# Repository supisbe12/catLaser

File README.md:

catLaser
---
A camera watches the room for your cat. When it detects motion, it figures out which direction the cat is moving and swings a laser dot slightly ahead of that movement — so the cat is always chasing something just out of reach rather than sitting on top of it. When the cat is finished it will point the laser at a dropper that will dispense treats. or when the cat disappears for a few seconds, it does a slow sweep to re-bait attention. After three minutes of nothing, it shuts the laser off and parks itself to save battery.
---
Screenshots
---

---
Hardware

Microcontroller: ESP32-S3-WROOM-1-N16R8 (Dual-core Xtensa LX7 @ up to 240MHz, 16MB Flash, 8MB Octal PSRAM)
Camera: Taidacent OV2640 2MP, connected via 24-pin 0.5mm FPC ribbon cable + ZIF socket
Power: Single 18650 Li-ion cell, onboard TP4056 charging via USB-C, MT3608 boost converter (stable 5V rail), AMS1117-3.3 LDO (3.3V rail)
Mounting: 3M Dual Lock strips — peel off to charge, click back into the same spot
---
Software
Unfinished(need parts)
---
Bill of Materials
https://docs.google.com/spreadsheets/d/1QPfYICotrgUIVAbHsGZsmmrA3oqBLHhNqElr4AwxpG0/edit?usp=sharing

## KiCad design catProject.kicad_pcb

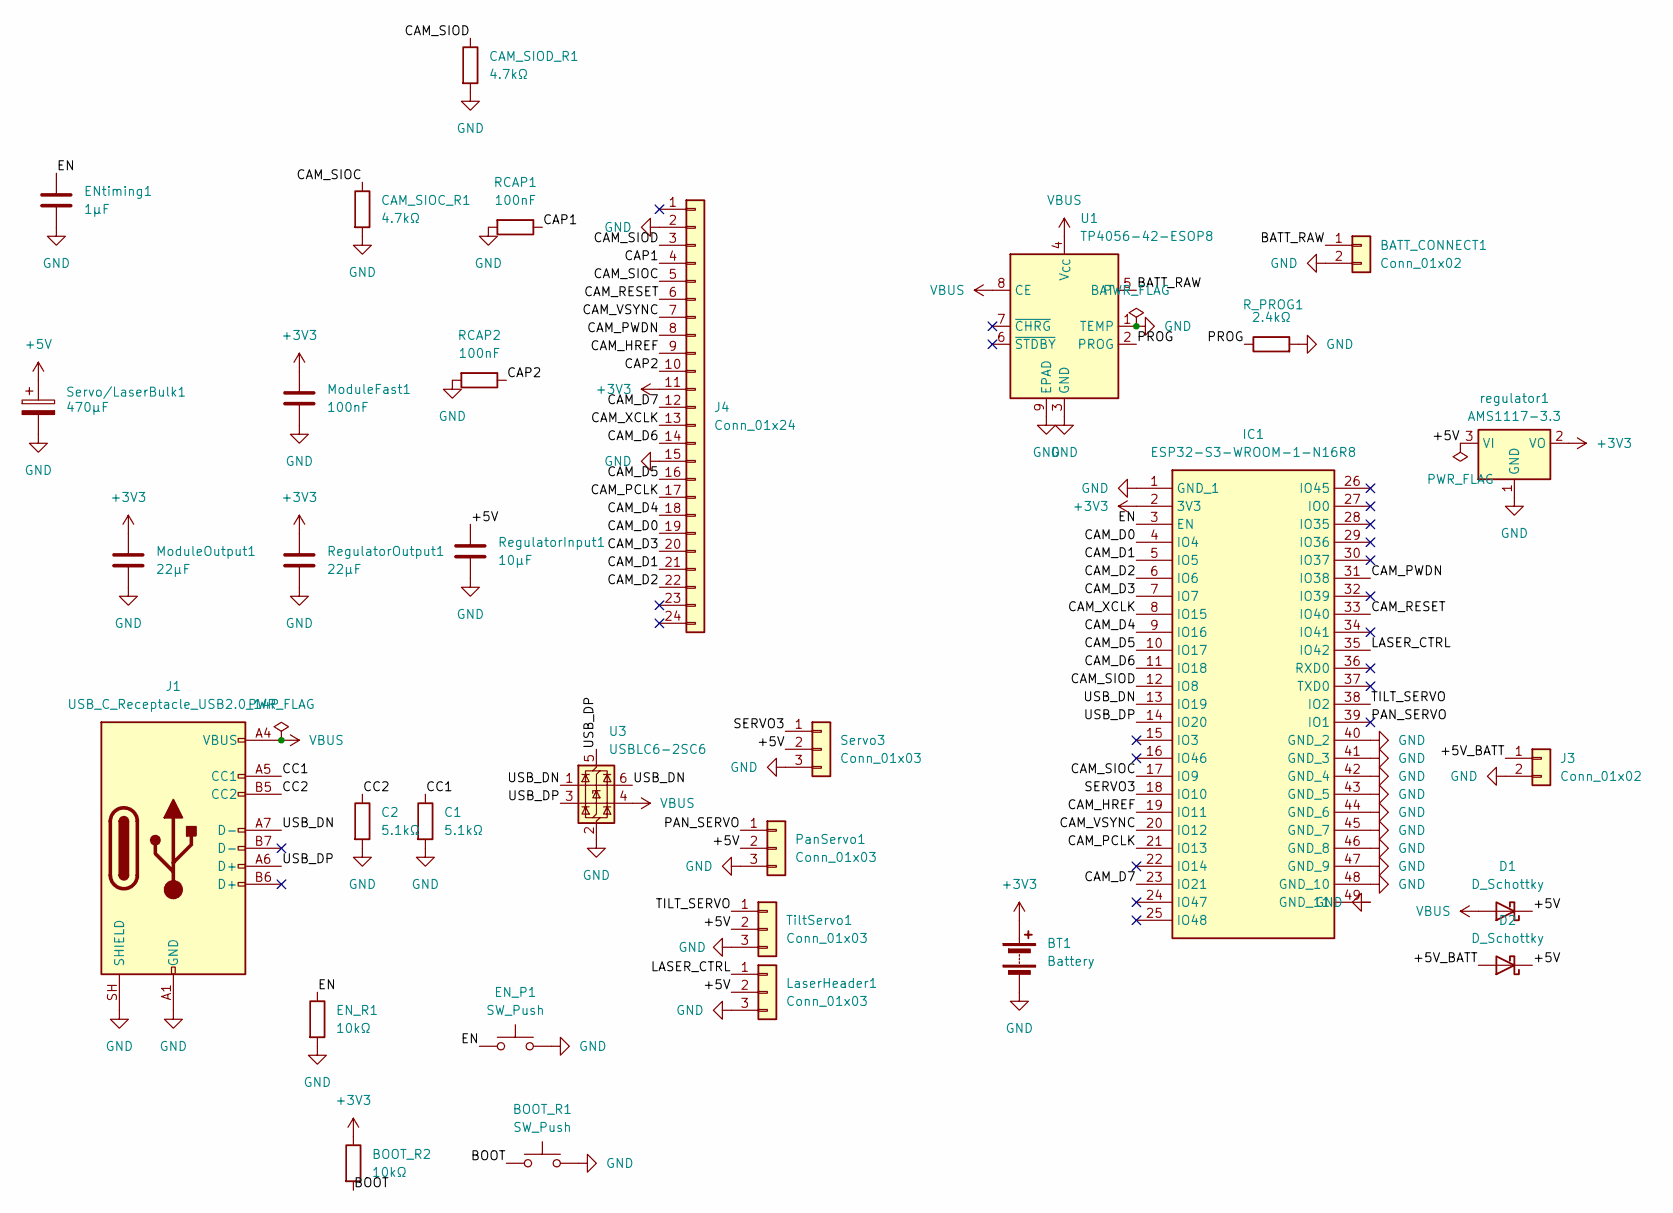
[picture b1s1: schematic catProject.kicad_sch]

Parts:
BATT_CONNECT1: Conn_01x02; PinHeader_1x02_P2.54mm_Vertical
BOOT_R1: SW_Push; SW_PUSH_6mm
BOOT_R2: 10kΩ; R_0805_2012Metric
BT1: Battery
C1, C2: 5.1kΩ; R_0805_2012Metric
CAM_SIOC_R1: 4.7kΩ
CAM_SIOD_R1: 4.7kΩ
D1, D2: D_Schottky; D_SMA
EN_P1: SW_Push; SW_PUSH_6mm
EN_R1: 10kΩ; R_0805_2012Metric
ENtiming1: 1µF; C_0805_2012Metric
IC1: ESP32-S3-WROOM-1-N16R8; ESP32S3WROOM1N16R8; Mouser Part Number 356-ESP32S3WRM1N16R8
J1: USB_C_Receptacle_USB2.0_14P; USB_C_Receptacle_GCT_USB4105-xx-A_16P_TopMnt_Horizontal
J3: Conn_01x02; PinHeader_1x02_P2.54mm_Vertical
J4: Conn_01x24; Hirose_FH12-24S-0.5SH_1x24-1MP_P0.50mm_Horizontal
LaserHeader1: Conn_01x03; PinHeader_1x03_P2.54mm_Vertical
ModuleFast1: 100nF; C_0805_2012Metric
ModuleOutput1: 22µF; C_0805_2012Metric
PanServo1: Conn_01x03; PinHeader_1x03_P2.54mm_Vertical
RCAP1, RCAP2: 100nF; R_0805_2012Metric
R_PROG1: 2.4kΩ; R_0805_2012Metric
RegulatorInput1: 10µF; C_0805_2012Metric
RegulatorOutput1: 22µF; C_0805_2012Metric
Servo3: Conn_01x03; PinHeader_1x03_P2.54mm_Vertical
Servo/LaserBulk1: 470µF; CP_Radial_D6.3mm_P2.50mm
TiltServo1: Conn_01x03; PinHeader_1x03_P2.54mm_Vertical
U1: TP4056-42-ESOP8; SOIC-8-1EP_3.9x4.9mm_P1.27mm_EP2.41x3.3mm
U3: USBLC6-2SC6; SOT-23-6
regulator1: AMS1117-3.3; SOT-223-3_TabPin2

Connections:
+3V3: BOOT_R2.1, BT1.1 (+), IC1.2 (3V3), J4.11, ModuleFast1.1, ModuleOutput1.1, RegulatorOutput1.1, regulator1.2 (VO)
+5V: D1.1 (K), D2.1 (K), LaserHeader1.2, PanServo1.2, RegulatorInput1.1, Servo3.2, Servo/LaserBulk1.1, TiltServo1.2, regulator1.3 (VI)
/+5V_BATT: D2.2 (A), J3.1
/BATT_RAW: BATT_CONNECT1.1, U1.5 (BAT); also elsewhere on the board
/BOOT: BOOT_R1.1, BOOT_R2.2
/CAM_D0: IC1.4 (IO4), J4.19
/CAM_D1: IC1.5 (IO5), J4.21
/CAM_D2: IC1.6 (IO6), J4.22
/CAM_D3: IC1.7 (IO7), J4.20
/CAM_D4: IC1.9 (IO16), J4.18
/CAM_D5: IC1.10 (IO17), J4.16
/CAM_D6: IC1.11 (IO18), J4.14
/CAM_D7: IC1.23 (IO21), J4.12
/CAM_HREF: IC1.19 (IO11), J4.9
/CAM_PCLK: IC1.21 (IO13), J4.17
/CAM_PWDN: IC1.31 (IO38), J4.8
/CAM_RESET: IC1.33 (IO40), J4.6
/CAM_SIOC: CAM_SIOC_R1.1, IC1.17 (IO9), J4.5
/CAM_SIOD: CAM_SIOD_R1.1, IC1.12 (IO8), J4.3
/CAM_VSYNC: IC1.20 (IO12), J4.7
/CAM_XCLK: IC1.8 (IO15), J4.13
/CAP1: J4.4, RCAP1.1
/CAP2: J4.10, RCAP2.1
/CC1: C1.1, J1.A5 (CC1)
/CC2: C2.1, J1.B5 (CC2)
/EN: EN_P1.1, EN_R1.1, ENtiming1.1, IC1.3 (EN)
/LASER_CTRL: IC1.35 (IO42), LaserHeader1.1
/PAN_SERVO: IC1.39 (IO1), PanServo1.1
/PROG: R_PROG1.1, U1.2 (PROG)
/SERVO3: IC1.18 (IO10), Servo3.1
/TILT_SERVO: IC1.38 (IO2), TiltServo1.1
/USB_DN: IC1.13 (IO19), J1.A7 (D-), U3.1 (I/O1), U3.6 (I/O1)
/USB_DP: IC1.14 (IO20), J1.A6 (D+), U3.3 (I/O2), U3.5 (VBUS)
GND: BATT_CONNECT1.2, BOOT_R1.2, BT1.2 (-), C1.2, C2.2, CAM_SIOC_R1.2, CAM_SIOD_R1.2, EN_P1.2, EN_R1.2, ENtiming1.2, IC1.1 (GND_1), IC1.40 (GND_2), IC1.41 (GND_3), IC1.42 (GND_4), IC1.43 (GND_5), IC1.44 (GND_6), IC1.45 (GND_7), IC1.46 (GND_8), IC1.47 (GND_9), IC1.48 (GND_10), IC1.49 (GND_11), J1.A1 (GND), J1.A12 (GND), J1.B1 (GND), J1.B12 (GND), J1.SH (SHIELD), J3.2, J4.2, J4.15, LaserHeader1.3, ModuleFast1.2, ModuleOutput1.2, PanServo1.3, RCAP1.2, RCAP2.2, R_PROG1.2, RegulatorInput1.2, RegulatorOutput1.2, Servo3.3, Servo/LaserBulk1.2, TiltServo1.3, U1.1 (TEMP), U1.3 (GND), U1.9 (EPAD), U3.2 (GND), regulator1.1 (GND); also elsewhere on the board
VBUS: D1.2 (A), J1.A4 (VBUS), J1.A9 (VBUS), J1.B4 (VBUS), J1.B9 (VBUS), U1.4 (V_{CC}), U1.8 (CE), U3.4 (I/O2)

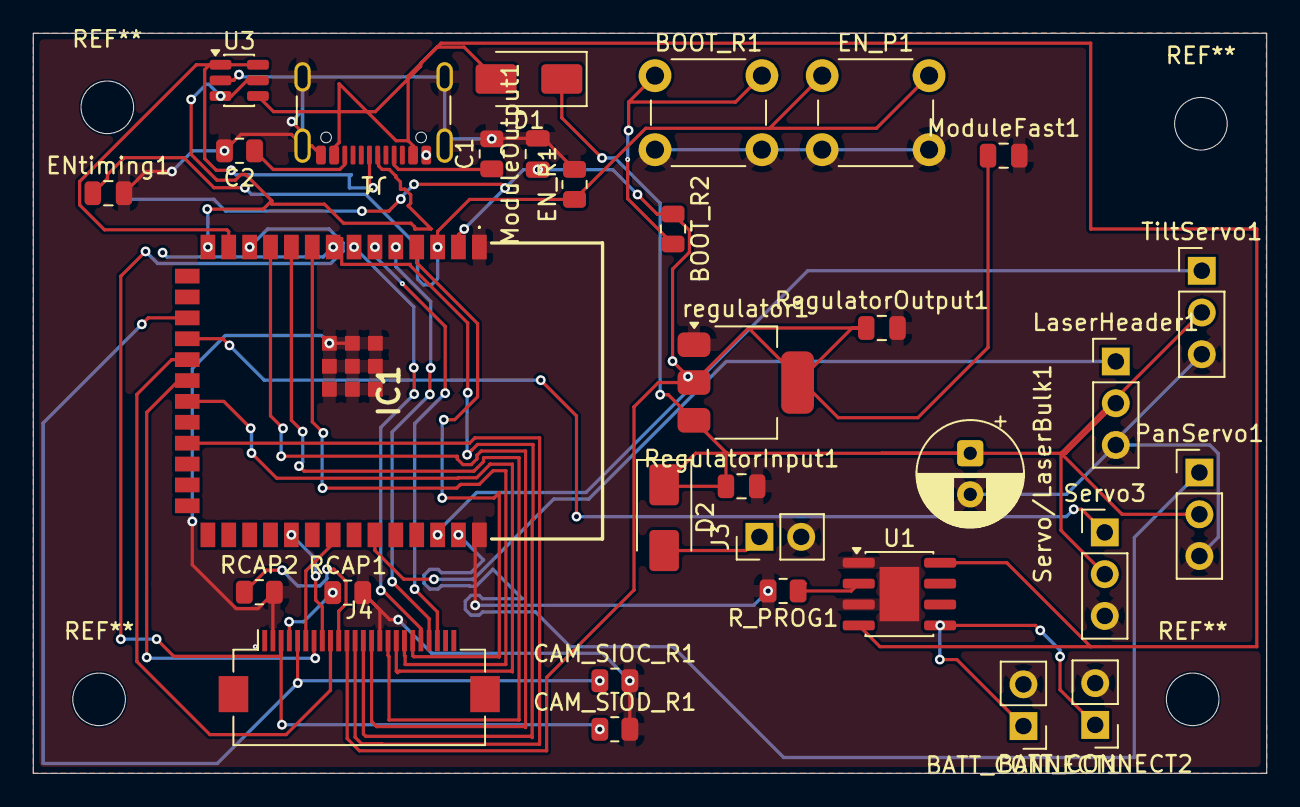
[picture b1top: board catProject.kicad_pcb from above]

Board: 2 copper layers, 75.0 x 45.0 mm, 32 parts (0 on the bottom side), 35 nets.

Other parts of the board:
BATT_CONNECT2: Conn_01x02; PinHeader_1x02_P2.54mm_Vertical

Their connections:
/BATT_RAW: BATT_CONNECT2.1; also elsewhere on the board
GND: BATT_CONNECT2.2; also elsewhere on the board

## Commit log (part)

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2026-06-30 Update journal with project progress and PCB design notes
    Documented the progress and challenges faced during the design of an automatic cat laser toy, including custom PCB design and troubleshooting.
2026-06-30 Add journal entries for cat laser toy project
    Documented the process of creating an automatic cat laser toy, including custom PCB design and troubleshooting experiences over several days.
2026-06-30 Document completion of PCB design with new connector
    Added details about finishing the PCB design and included an image.
2026-06-30 Refine journal entries and PCB design updates
    Updated journal entries for clarity and added details about the PCB design process, including challenges faced and solutions implemented.
2026-06-30 Update journal with PCB design progress for Days 4-6
    Added entries for Days 4, 5, and 6 of PCB design progress, detailing troubleshooting, footprint assignment, and research on camera compatibility.
2026-06-30 Update journal with entries for Day 4 and Day 5
